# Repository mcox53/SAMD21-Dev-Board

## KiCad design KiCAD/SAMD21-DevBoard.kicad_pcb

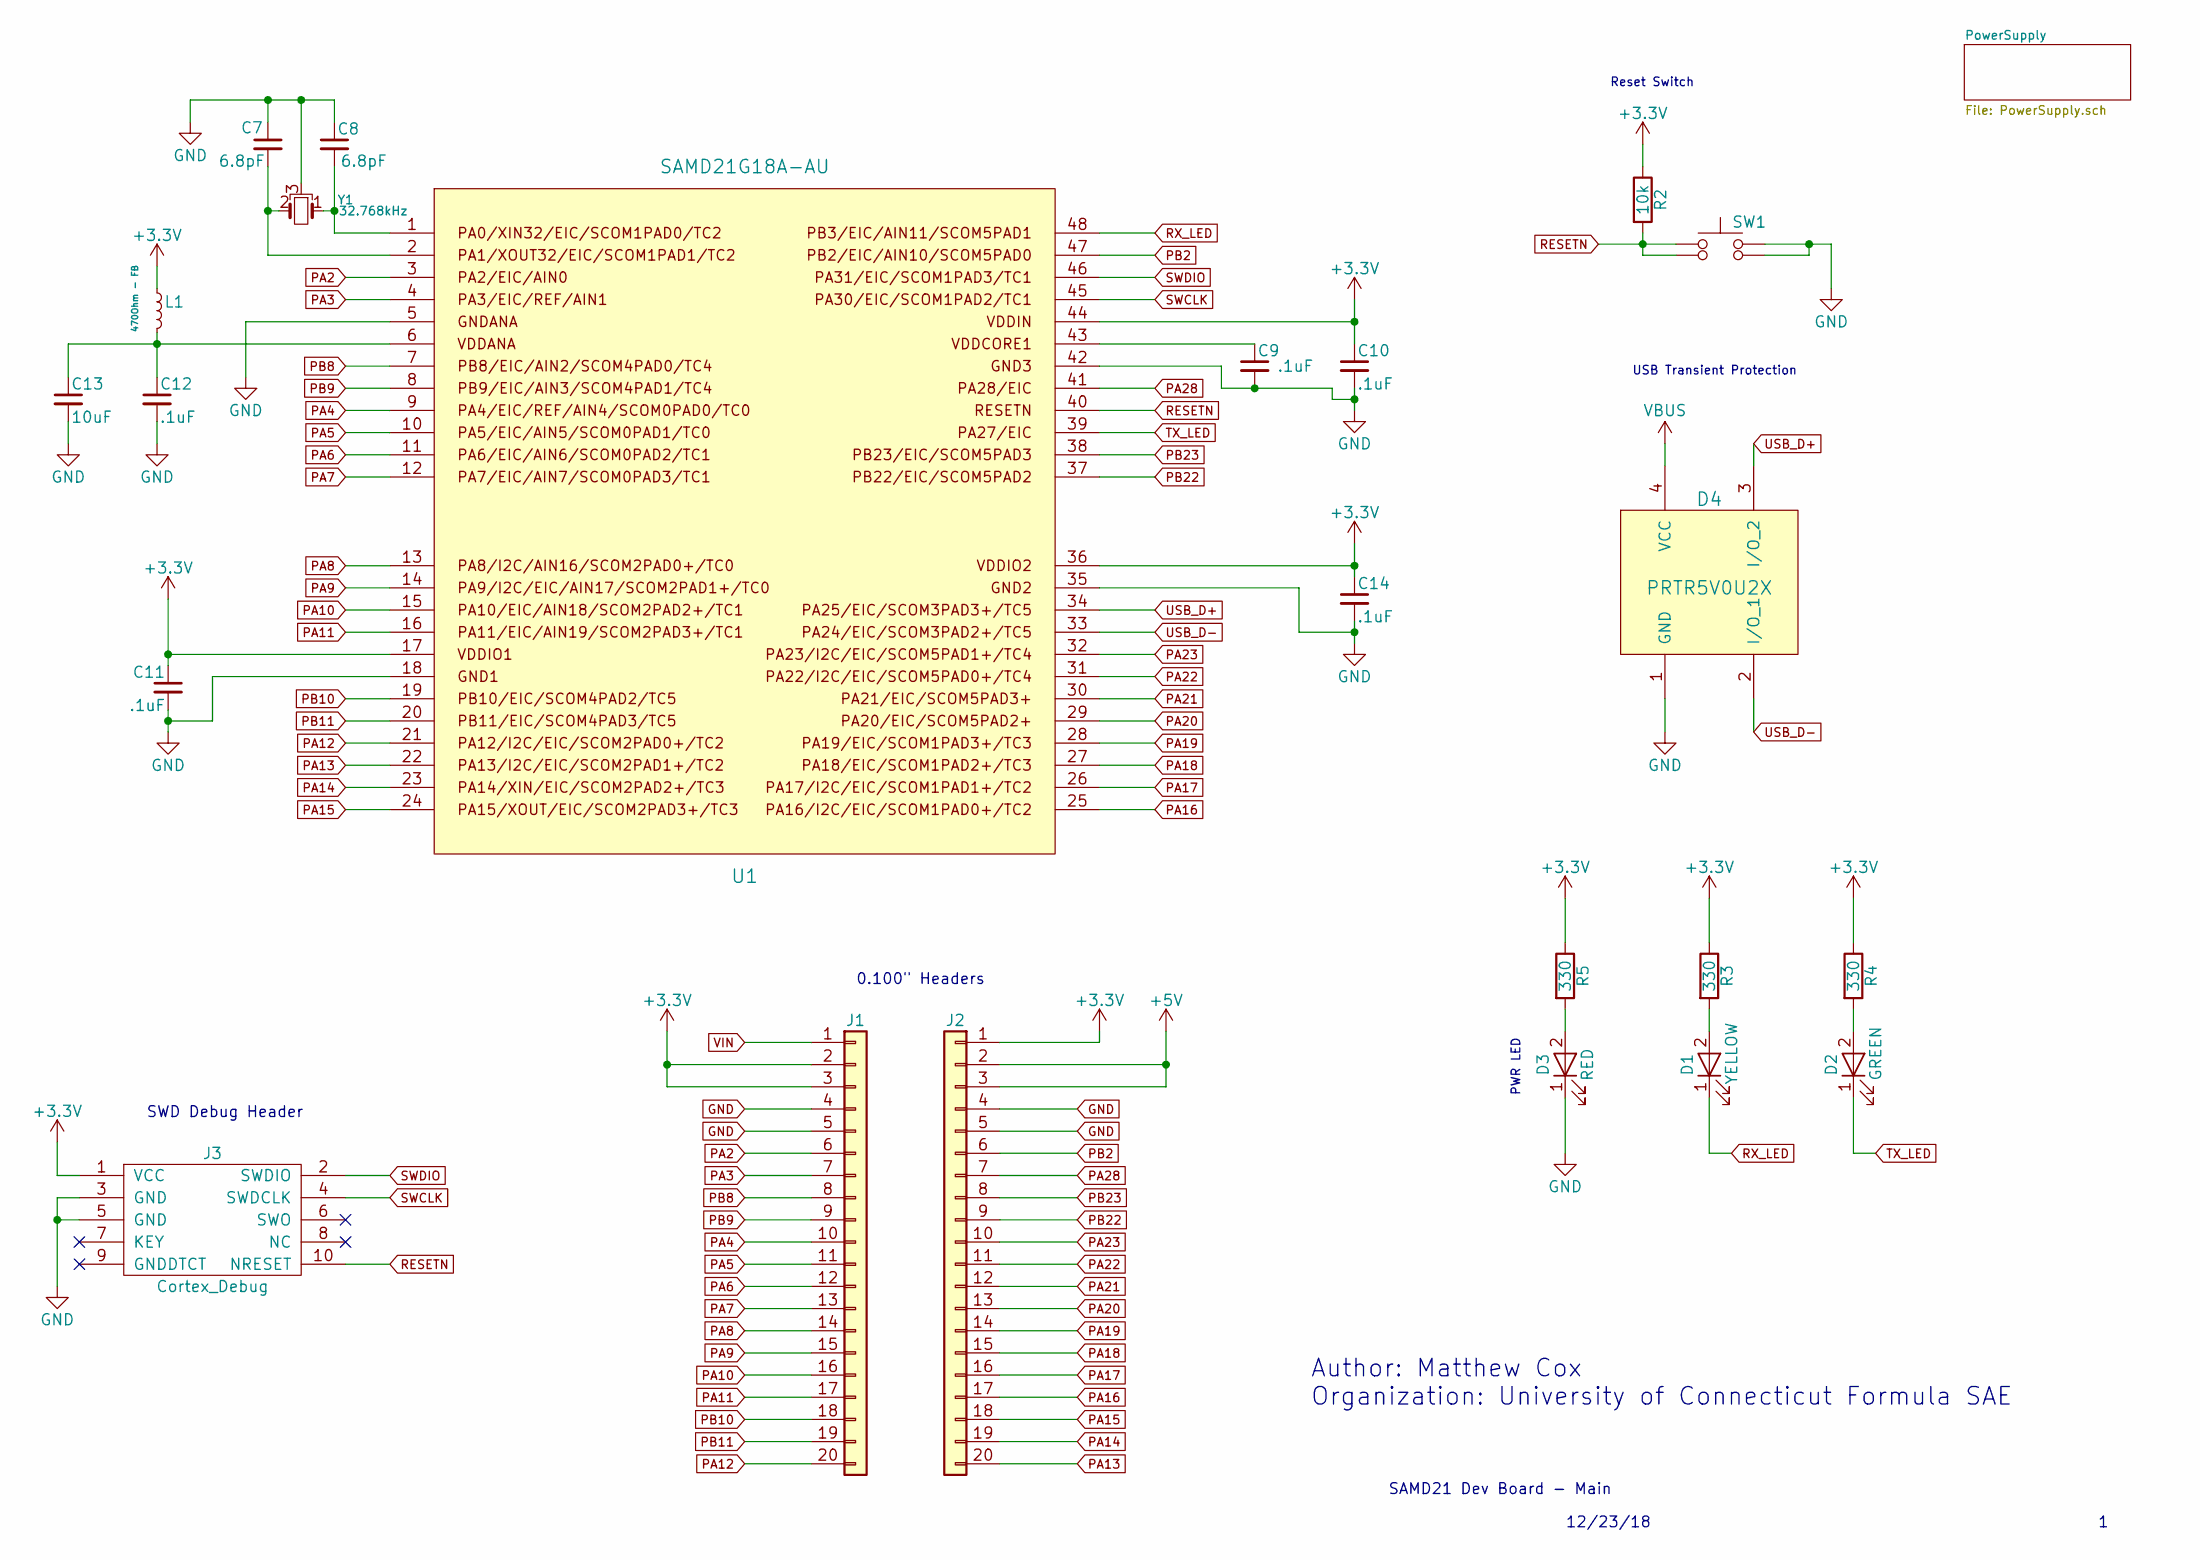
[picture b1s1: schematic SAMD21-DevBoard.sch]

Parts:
C7, C8: 6.8pF; C_0805
C9, C10, C11, C12, C14: .1uF; C_1206
C13: 10uF; C_1206
D1: YELLOW; LED_1206
D2: GREEN; LED_1206
D3: RED; LED_1206
D4: PRTR5V0U2X; SOT-143
J1, J2: .1\" Headers; Pin_Header_Straight_1x20_Pitch2.54mm
J3: Cortex_Debug; Pin_Header_Straight_2x05_Pitch1.27mm
L1: 470Ohm - FB; L_1806
R2: 10k; R_1210
R3, R4, R5: 330; R_1210
SW1: FSMCTTR
U1: SAMD21G18A-AU; QFP50P900X900X120-48N
Y1: 32.768kHz; MS1V-T1K

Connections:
+3V3: C10.1, C11.1, C14.1, J1.2, J1.3, J2.1, J3.1 (VCC), L1.1, R2.1, R3.1, R4.1, R5.1, U1.17, U1.36, U1.44; also elsewhere on the board
+5V: J2.2, J2.3; also elsewhere on the board
GND: C7.1, C8.1, C9.2, C10.2, C11.2, C12.2, C13.2, C14.2, D3.1 (K), D4.1 (GND), J1.4, J1.5, J2.4, J2.5, J3.3 (GND), J3.5 (GND), SW1.3, SW1.4, U1.5, U1.18, U1.35, U1.42, Y1.3; also elsewhere on the board
unnamed: C7.2, U1.2, Y1.2
unnamed: C8.2, U1.1, Y1.1
unnamed: C9.1, U1.43
unnamed: C12.1, C13.1, L1.2, U1.6
unnamed: D1.2 (A), R3.2
unnamed: D2.2 (A), R4.2
unnamed: D3.2 (A), R5.2
PA2: J1.6, U1.3
PA3: J1.7, U1.4
PA4: J1.10, U1.9
PA5: J1.11, U1.10
PA6: J1.12, U1.11
PA7: J1.13, U1.12
PA8: J1.14, U1.13
PA9: J1.15, U1.14
PA10: J1.16, U1.15
PA11: J1.17, U1.16
PA12: J1.20, U1.21
PA13: J2.20, U1.22
PA14: J2.19, U1.23
PA15: J2.18, U1.24
PA16: J2.17, U1.25
PA17: J2.16, U1.26
PA18: J2.15, U1.27
PA19: J2.14, U1.28
PA20: J2.13, U1.29
PA21: J2.12, U1.30
PA22: J2.11, U1.31
PA23: J2.10, U1.32
PA28: J2.7, U1.41
PB2: J2.6, U1.47
PB8: J1.8, U1.7
PB9: J1.9, U1.8
PB10: J1.18, U1.19
PB11: J1.19, U1.20
PB22: J2.9, U1.37
PB23: J2.8, U1.38
RESETN: J3.10 (NRESET), R2.2, SW1.1, SW1.2, U1.40
RX_LED: D1.1 (K), U1.48
SWCLK: J3.4 (SWDCLK), U1.45
SWDIO: J3.2 (SWDIO), U1.46
TX_LED: D2.1 (K), U1.39
USB_D+: D4.3 (I/O_2), U1.34; also elsewhere on the board
USB_D-: D4.2 (I/O_1), U1.33; also elsewhere on the board
VBUS: D4.4 (VCC); also elsewhere on the board
VIN: J1.1; also elsewhere on the board

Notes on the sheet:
0.100" Headers
SWD Debug Header
PWR LED
Reset Switch
USB Transient Protection
SAMD21 Dev Board - Main
12/23/18
Author: Matthew Cox Organization: University of Connecticut Formula SAE

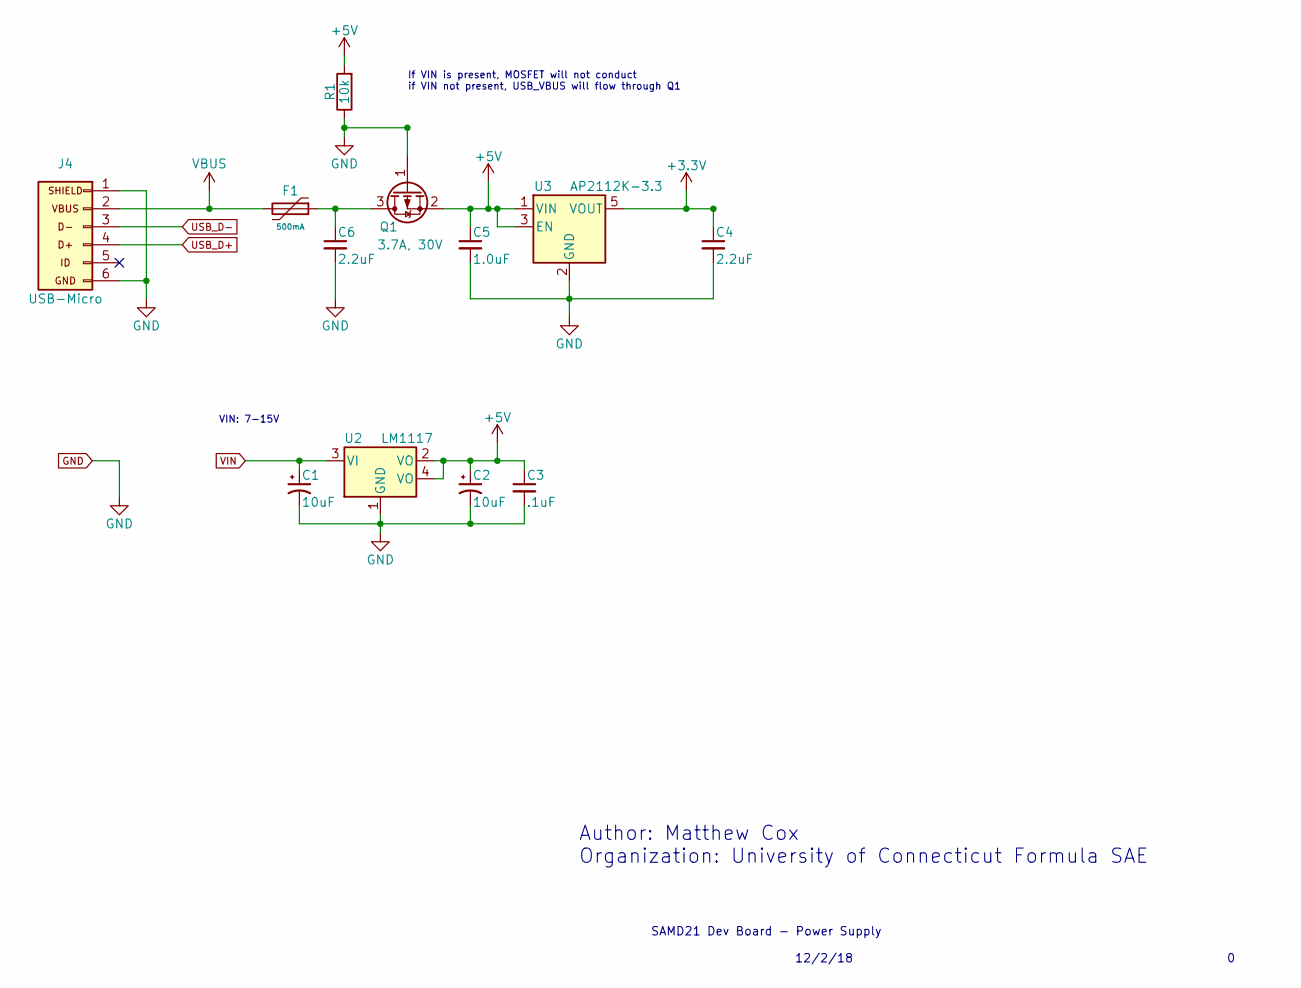
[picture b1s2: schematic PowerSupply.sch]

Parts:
C1, C2: 10uF; C_1206
C3: .1uF; C_1206
C4, C6: 2.2uF; C_1210
C5: 1.0uF; C_1210
F1: 500mA; R_1210
J4: USB-Micro; 10118192-0001LF
Q1: 3.7A, 30V; SOT-23
R1: 10k; R_1210
U2: LM1117; SOT-223
U3: AP2112K-3.3; SOT-23-5

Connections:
+3V3: C4.1, U3.5 (VOUT); also elsewhere on the board
+5V: C2.1, C3.1, C5.1, Q1.2 (S), R1.2, U2.2 (VO), U2.4 (VO), U3.1 (VIN), U3.3 (EN); also elsewhere on the board
GND: C1.2, C2.2, C3.2, C4.2, C5.2, C6.2, J4.1 (SHIELD), J4.6 (GND), Q1.1 (G), R1.1, U2.1 (GND), U3.2 (GND); also elsewhere on the board
unnamed: C6.1, F1.1, Q1.3 (D)
USB_D+: J4.4 (D+); also elsewhere on the board
USB_D-: J4.3 (D-); also elsewhere on the board
VBUS: F1.2, J4.2 (VBUS); also elsewhere on the board
VIN: C1.1, U2.3 (VI); also elsewhere on the board

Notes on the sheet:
VIN: 7-15V
If VIN is present, MOSFET will not conduct if VIN not present, USB_VBUS will flow through Q1
SAMD21 Dev Board - Power Supply
12/2/18
Author: Matthew Cox Organization: University of Connecticut Formula SAE

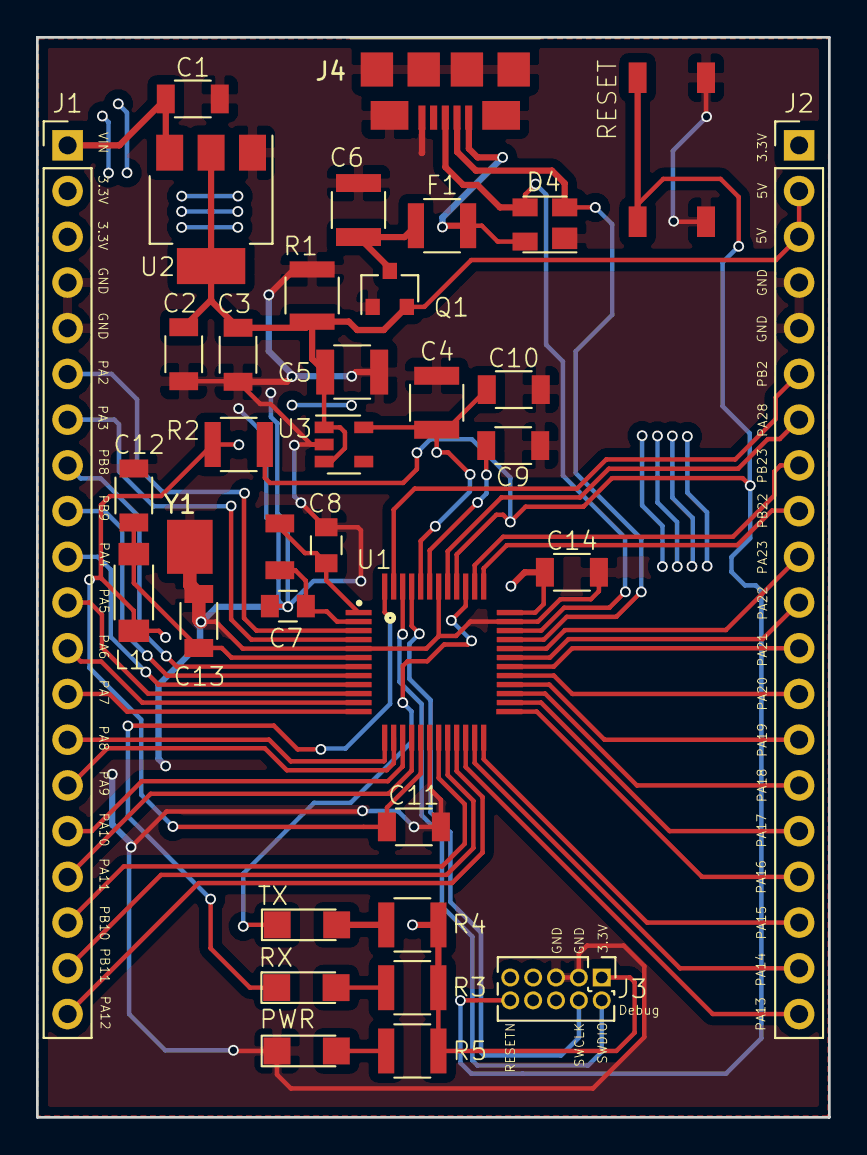
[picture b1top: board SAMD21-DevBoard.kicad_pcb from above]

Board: 2 copper layers, 44.0 x 60.0 mm, 35 parts (0 on the bottom side), 50 nets.

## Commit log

2018-11-19 Imported libraries from Dashboard PCB for usage
2018-11-19 Created Schematic Symbols for fuse, USB Connector, 5V and 3.3V regulator
2018-11-19 Made it through most of power supply schematic
2018-11-19 Made Cortex Debug Schematic Symbol
2018-11-19 Broke out pins from MCU and added data bus protection diode
2018-12-01 Created library for 4 pin SPST switch
2018-12-01 Editing capacitor values, prepping for layout phase
2018-12-02 Add TX & RX LEDs, tweak values
2018-12-02 Import SAMD21G18A-AU Footprint
2018-12-02 Schematic Rev 0
2018-12-02 Created footprints for switch, micro usb port and crystal
2018-12-06 Generate netlist and begin layout
2018-12-08 Board layout and fixing schematic errors
2018-12-08 Custom LM1117 Library
    Created a LM1117 library that has the tab (Pin 4) connected to the voltage output.
2018-12-09 Place and route
2018-12-21 Created schematic symbol and footprint for new tactile switch
2018-12-21 Revising layout with different board outline
2018-12-23 Fixed pad numbers in footprint to match connector
2018-12-23 More routing
2018-12-23 Finished routing, now fine tweaking and tuning
2018-12-24 Attempting to increase top flood plane connectivity
2018-12-24 Fix library error
2018-12-24 Schematic Rev 1
2018-12-24 Simulations verifying mosfet switching circuit
2019-01-19 Fixed pad spacing on USB connector
2019-01-19 Added GND connection to pad 3
2019-01-19 Revised crystal symbol and updated layout slightly
2019-01-19 Schematic Rev 2 (Production 1)
2019-01-19 PCB Rev 0 (Production 1)
2019-02-03 Updated temporary copy of dev board firmware. See README for more
